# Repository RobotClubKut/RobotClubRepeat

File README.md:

# RobotClubRepeat
ろぼっとくらぶ りぴ～と

キャチロボがんばりましょう

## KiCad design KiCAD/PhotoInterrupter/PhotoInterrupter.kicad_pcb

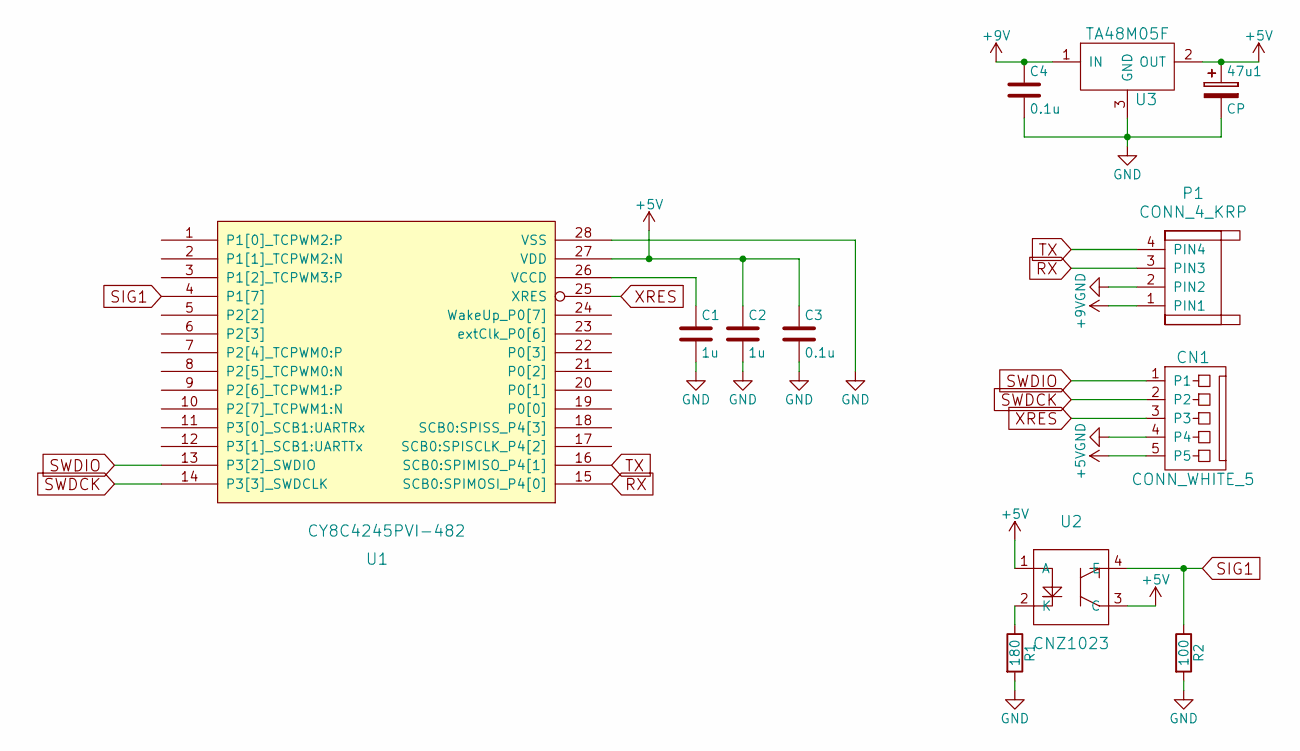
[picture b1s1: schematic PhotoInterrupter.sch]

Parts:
47u1: CP; C_Radial_D5_L6_P2.5
C1, C2: 1u; C_0805
C3, C4: 0.1u; C_0603
CN1: CONN_WHITE_5; DF1E-5P_Streight
P1: CONN_4_KRP; DF1E-4P_Streight
R1: 180; Diode_DO-41_SOD81_Vertical_AnodeUp
R2: 100; Diode_DO-41_SOD81_Vertical_AnodeUp
U1: CY8C4245PVI-482; SSOP-28_5.3x10.2mm_Pitch0.65mm
U2: CNZ1023
U3: TA48M05F; TO-251

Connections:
+5V: 47u1.1, C2.1, C3.1, CN1.5, U1.27 (VDD), U2.1 (A), U2.3 (C), U3.2 (OUT)
+9V: C4.1, P1.1 (PIN1), U3.1 (IN)
GND: 47u1.2, C1.2, C2.2, C3.2, C4.2, CN1.4, P1.2 (PIN2), R1.2, R2.2, U1.28 (VSS), U3.3 (GND)
unnamed: C1.1, U1.26 (VCCD)
unnamed: R1.1, U2.2 (K)
RX: P1.3 (PIN3), U1.15 (SCB0:SPIMOSI_P4[0])
SIG1: R2.1, U1.4 (P1[7]), U2.4 (E)
SWDCK: CN1.2, U1.14 (P3[3]_SWDCLK)
SWDIO: CN1.1, U1.13 (P3[2]_SWDIO)
TX: P1.4 (PIN4), U1.16 (SCB0:SPIMISO_P4[1])
XRES: CN1.3, U1.25 (XRES)

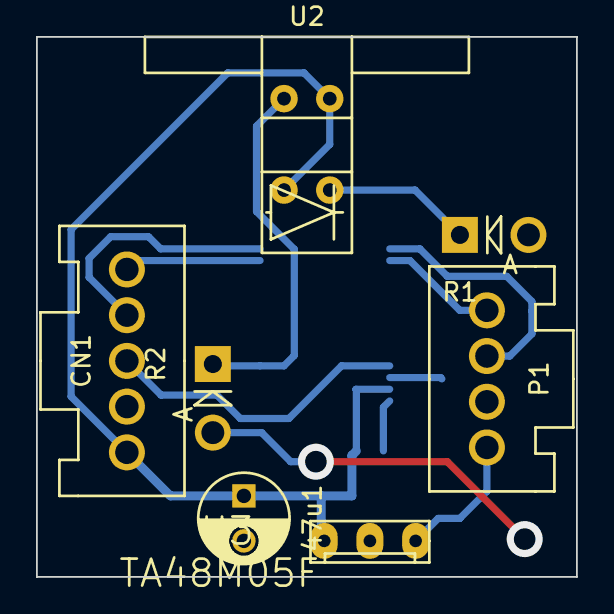
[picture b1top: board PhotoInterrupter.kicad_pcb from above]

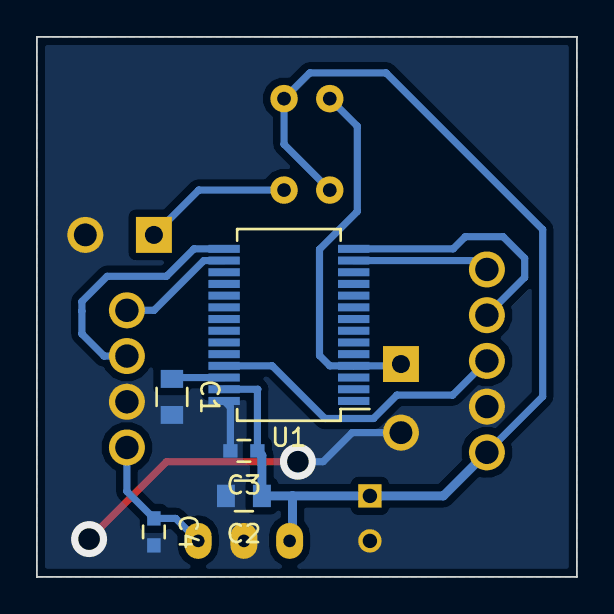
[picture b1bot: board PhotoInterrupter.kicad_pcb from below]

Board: 2 copper layers, 30.0 x 30.0 mm, 12 parts (5 on the bottom side), 11 nets.

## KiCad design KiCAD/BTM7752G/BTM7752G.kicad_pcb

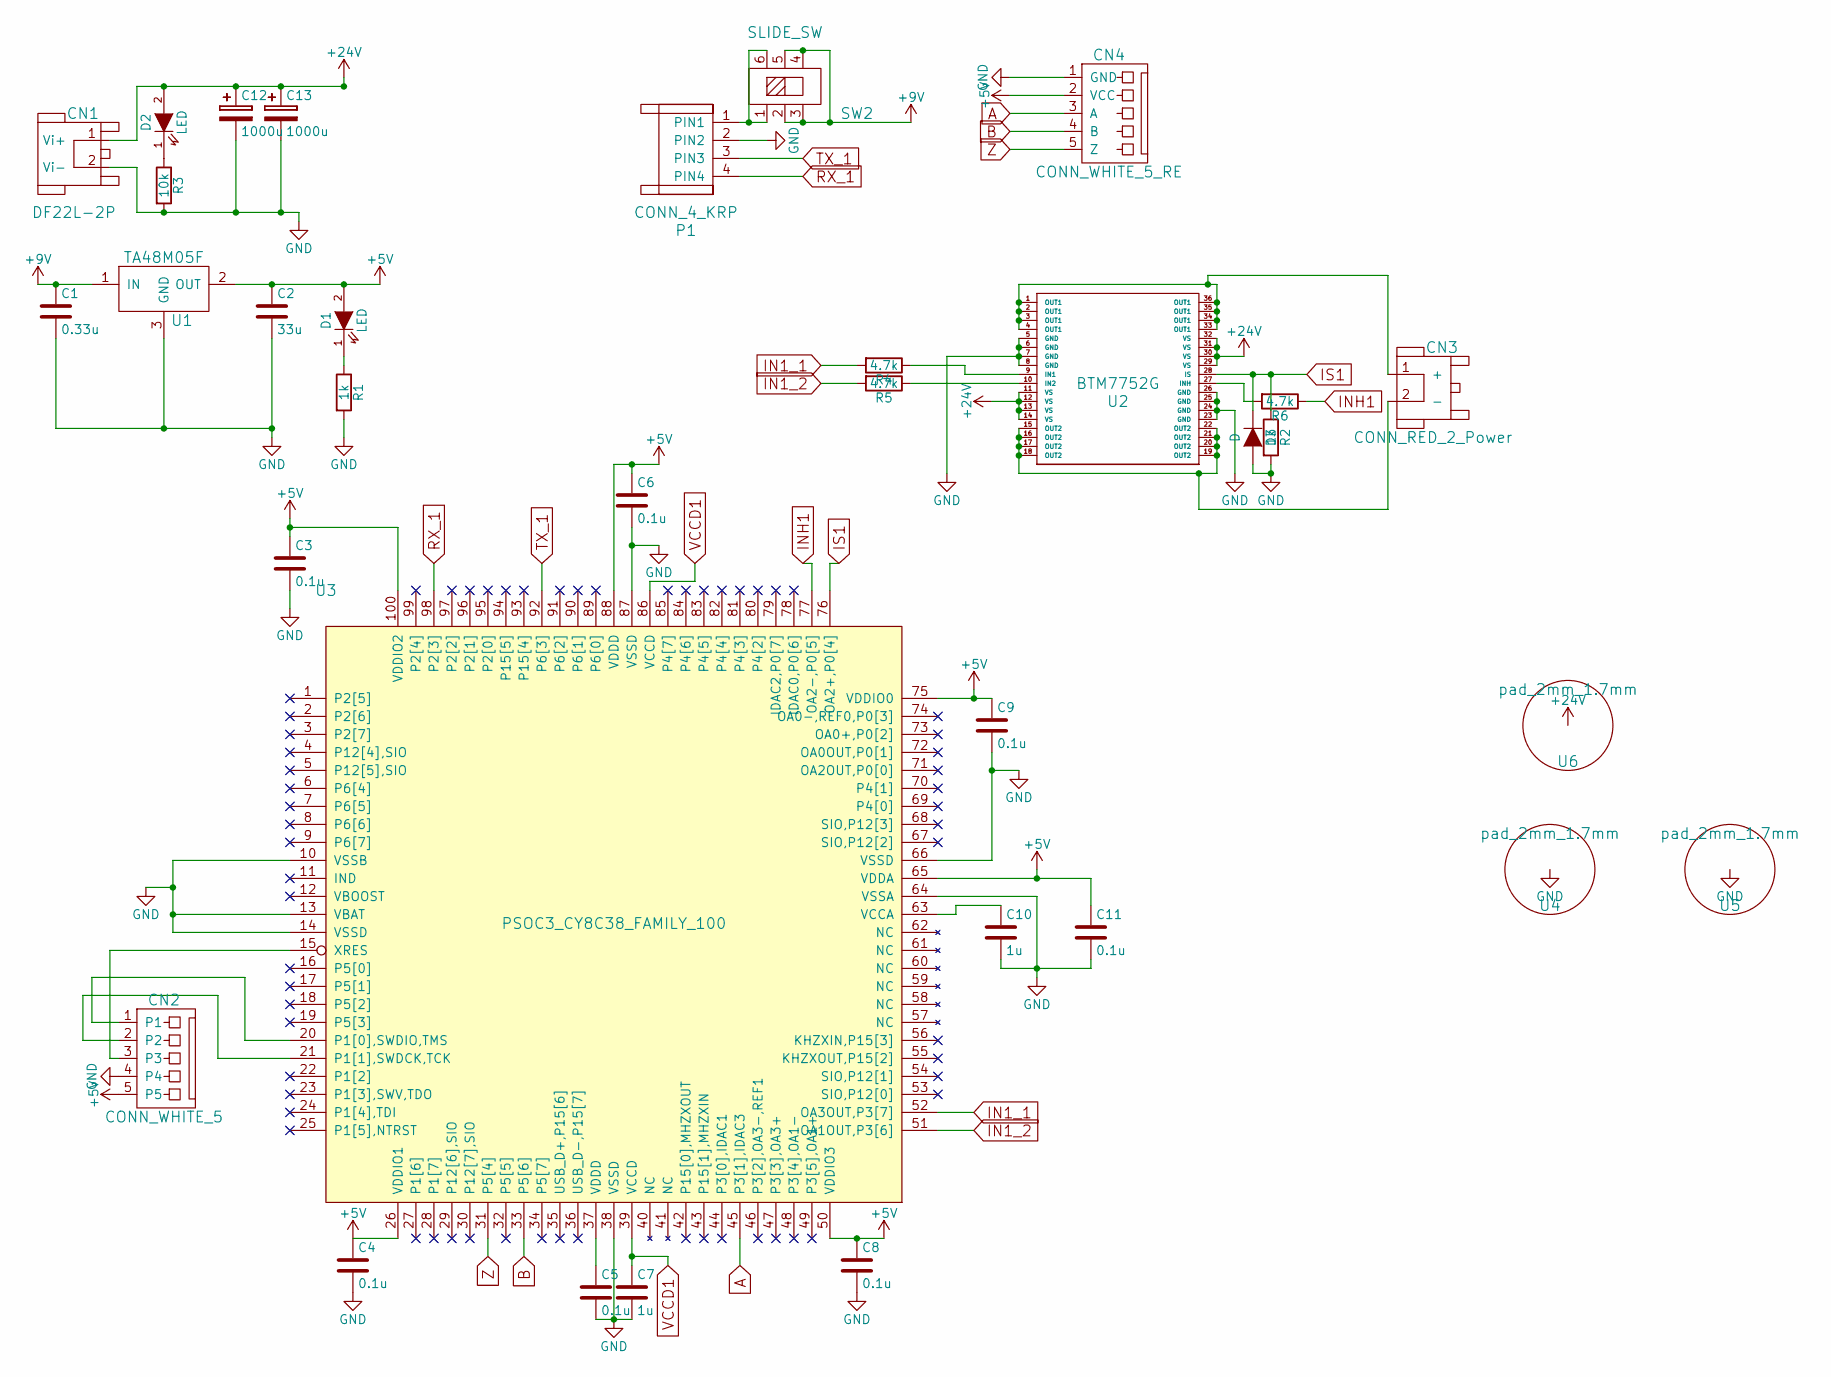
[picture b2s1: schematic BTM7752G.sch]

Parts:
C1: 0.33u; C_0603
C2: 33u; C_Radial_D5_L6_P2.5
C3, C4, C5, C6, C8, C9, C11: 0.1u; C_0603
C7, C10: 1u; C_0805
C12: 1000u; C_Radial_D18_L36_P7.5_Horizon5
C13: 1000u; C_Radial_D18_L36_P7.5_Horizon6
CN1: DF22L-2P; CONN_RED_2P_STRAIGHT
CN2: CONN_WHITE_5; DF1E-5P_Streight
CN3: CONN_RED_2_Power; CONN_RED_2P_STRAIGHT
CN4: CONN_WHITE_5_RE; DF1E-5P_Streight
D1, D2: LED; LED-3MM
D3: D; SOD-523_1
P1: CONN_4_KRP; DF1E-4P_Streight
R1, R2: 1k; R_0603
R3: 10k; R_0603
R4, R5, R6: 4.7k; R_0603
SW2: SLIDE_SW; Slide_Switch_SMD
U1: TA48M05F; HSOP3-P-2
U2: BTM7752G; PG-DSO-36
U3: PSOC3_CY8C38_FAMILY_100; TQFP-100_14x14mm_Pitch0.5mm
U4, U5, U6: pad_2mm_1.7mm

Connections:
+5V: C2.1, C3.1, C4.1, C6.1, C8.1, C9.1, C11.1, CN2.5, CN4.2 (VCC), D1.2 (A), U1.2 (OUT), U3.26 (VDDIO1), U3.50 (VDDIO3), U3.65 (VDDA), U3.75 (VDDIO0), U3.88 (VDDD), U3.100 (VDDIO2)
+9V: C1.1, SW2.2, SW2.3, SW2.4, SW2.5, U1.1 (IN)
+24V: C12.1, C13.1, CN1.1 (Vi+), D2.2 (A), U2.11 (VS), U2.12 (VS), U2.13 (VS), U2.14 (VS), U2.29 (VS), U2.30 (VS), U2.31 (VS), U2.32 (VS), U6.1
A: CN4.3 (A), U3.45 (P3[1],IDAC3)
B: CN4.4 (B), U3.33 (P5[6])
GND: C1.2, C2.2, C3.2, C4.2, C5.2, C6.2, C7.2, C8.2, C9.2, C10.2, C11.2, C12.2, C13.2, CN1.2 (Vi-), CN2.4, CN4.1 (GND), D3.2 (A), P1.2 (PIN2), R1.2, R2.2, R3.2, U1.3 (GND), U2.5 (GND), U2.6 (GND), U2.7 (GND), U2.8 (GND), U2.23 (GND), U2.24 (GND), U2.25 (GND), U2.26 (GND), U3.10 (VSSB), U3.13 (VBAT), U3.14 (VSSD), U3.38 (VSSD), U3.64 (VSSA), U3.66 (VSSD), U3.87 (VSSD), U4.1, U5.1
IN1_1: R4.2, U3.52 (OA3OUT,P3[7])
IN1_2: R5.2, U3.51 (OA1OUT,P3[6])
INH1: R6.1, U3.77 (OA2-,P0[5])
IS1: D3.1 (K), R2.1, U2.28 (IS), U3.76 (OA2+,P0[4])
unnamed: C5.1, U3.37 (VDDD)
unnamed: C10.1, U3.63 (VCCA)
unnamed: CN2.1, U3.20 (P1[0],SWDIO,TMS)
unnamed: CN2.2, U3.21 (P1[1],SWDCK,TCK)
unnamed: CN2.3, U3.15 (XRES)
unnamed: CN3.1 (+), U2.1 (OUT1), U2.2 (OUT1), U2.3 (OUT1), U2.4 (OUT1), U2.33 (OUT1), U2.34 (OUT1), U2.35 (OUT1), U2.36 (OUT1)
unnamed: CN3.2 (-), U2.15 (OUT2), U2.16 (OUT2), U2.17 (OUT2), U2.18 (OUT2), U2.19 (OUT2), U2.20 (OUT2), U2.21 (OUT2), U2.22 (OUT2)
unnamed: D1.1 (K), R1.1
unnamed: D2.1 (K), R3.1
unnamed: P1.1 (PIN1), SW2.1, SW2.6
unnamed: R4.1, U2.9 (IN1)
unnamed: R5.1, U2.10 (IN2)
unnamed: R6.2, U2.27 (INH)
RX_1: P1.4 (PIN4), U3.98 (P2[3])
TX_1: P1.3 (PIN3), U3.92 (P6[3])
VCCD1: C7.1, U3.39 (VCCD), U3.86 (VCCD)
Z: CN4.5 (Z), U3.31 (P5[4])

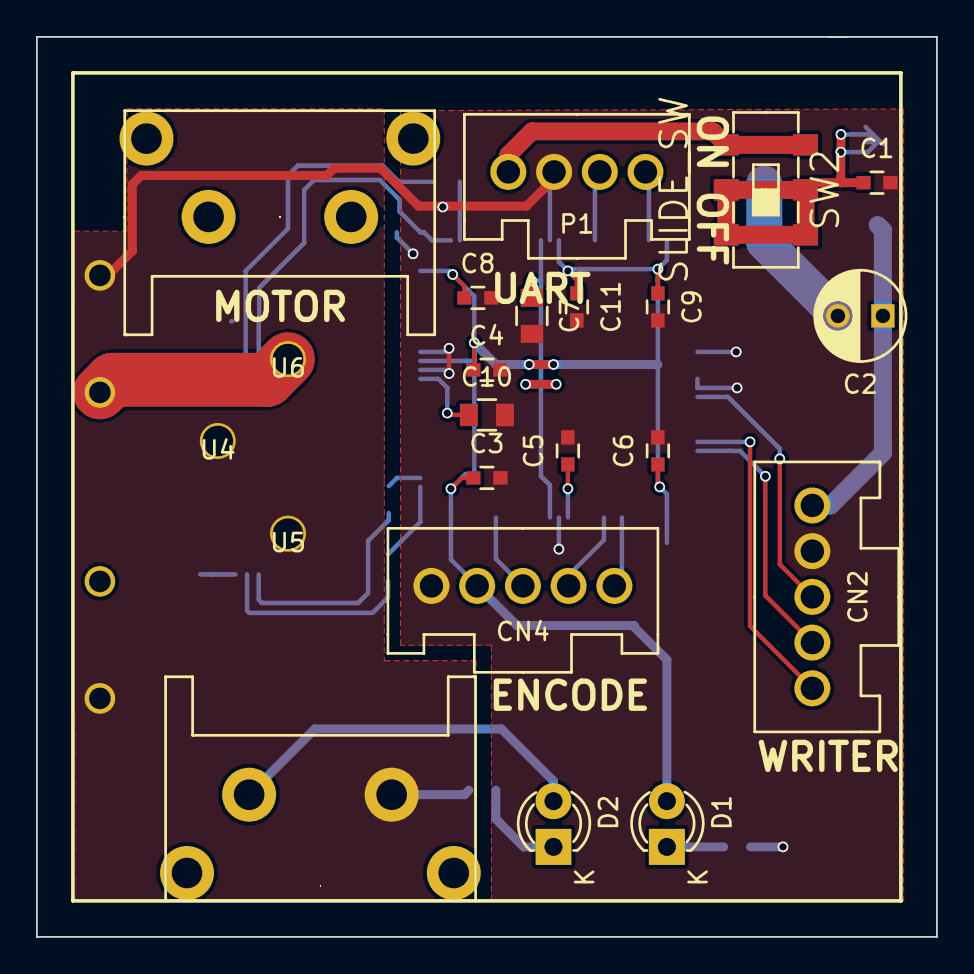
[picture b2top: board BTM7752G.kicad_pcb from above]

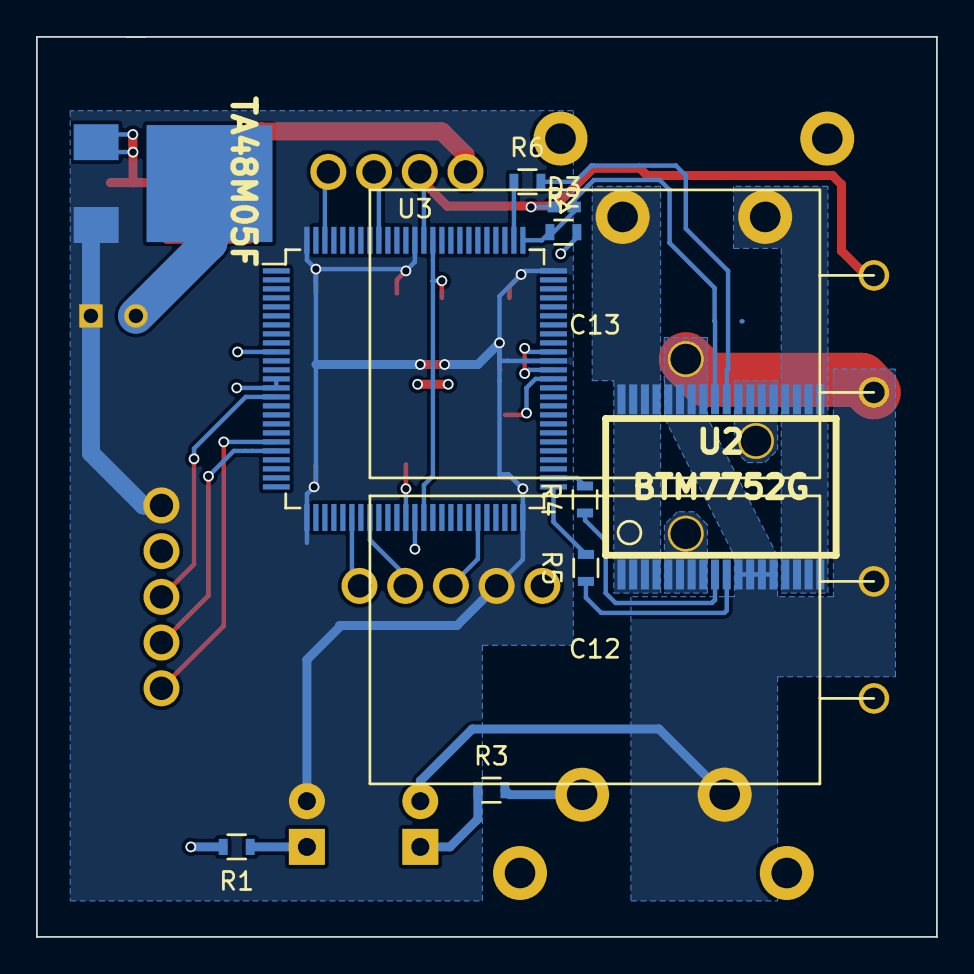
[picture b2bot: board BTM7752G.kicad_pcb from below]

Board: 2 copper layers, 50.0 x 50.0 mm, 34 parts (12 on the bottom side), 27 nets.

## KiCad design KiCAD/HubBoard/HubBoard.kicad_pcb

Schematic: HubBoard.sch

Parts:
C3, C4, C5, C7, C8, C10, C16, C17, C18, C22, C24, C25, C26, C28, C29: 0.1u; C_0603
C6, C11, C19, C23: 1u; C_0805
C9: 470p; C_Disc_D6_P5
C12, C13, C20, C21: 12p; C_0603
C27: 33u; C_Radial_D5_L6_P2.5
CN1, CN3: CONN_WHITE_5; DF1E-5P_Streight
CN2: DF22L-2P; CONN_RED_2P
CN4: DF22R-2P; CONN_RED_2P
CN5, CN6: CONN_WHITE_3; DF1E-3P_Streight
CP1: 470u; C_Radial_D10_L13_P5
CP2: 100u; C_Radial_D10_L13_P5
D1: D; Diode_DO-41_SOD81_Vertical_AnodeUp
D2: LED; LED-3MM
D3, D4, D7, D8, D9, D10: LED; LED-0603
L1: 220u; C_Radial_D10_L20_P5
R1: 1k; Resistor_Horizontal_RM10mm
R2: 6.2k; Resistor_Horizontal_RM10mm
R3: 0.33; Resistor_Horizontal_RM10mm
R4: R; R_0603
R5, R6, R9, R10, R11, R12: 1k; R_0603
SW1: SLIDE_SW; Toggle_Swith
U1, U2, U3, U4: DF3_UART; DF1E-4P_Streight
U5: TA48M05F; TO-251
U6: NJM2360A; PDIP-8
U7: Mini-B; USB_MINI_B_HIROSE
U8, U10: PSOC3_CY8C38_FAMILY_100; TQFP-100_14x14mm_Pitch0.5mm
U9, U11, U12, U13: drill_3mm; dril_3mm
Y1, Y2: Crystal; Crystal_HC49-SD_SMD

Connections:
+5V: C3.1, C4.1, C5.1, C7.1, C8.1, C16.1, C18.1, C22.1, C24.1, C25.1, C27.1, C28.1, C29.1, CN1.5, CN3.5, D2.2, U5.2 (OUT), U8.26 (VDDIO1), U8.50 (VDDIO3), U8.65 (VDDA), U8.75 (VDDIO0), U8.88 (VDDD), U8.100 (VDDIO2), U10.26 (VDDIO1), U10.50 (VDDIO3), U10.65 (VDDA), U10.75 (VDDIO0), U10.88 (VDDD), U10.100 (VDDIO2)
+9V: C26.1, CP1.1, L1.1, R2.1, U1.1 (VCC), U2.1 (VCC), U3.1 (VCC), U4.1 (VCC), U5.1 (IN)
+24V: CP2.1, R3.1, SW1.3, U6.6 (V+)
/bus0: U8.98 (P2[3]), U10.89 (P6[0])
/bus1: U8.97 (P2[2]), U10.90 (P6[1])
/bus2: U8.96 (P2[1]), U10.91 (P6[2])
/bus3: U8.95 (P2[0]), U10.92 (P6[3])
/bus4: U8.94 (P15[5]), U10.93 (P15[4])
/bus5: U8.93 (P15[4]), U10.94 (P15[5])
/bus6: U8.92 (P6[3]), U10.95 (P2[0])
/bus7: U8.91 (P6[2]), U10.96 (P2[1])
/bus8: U8.90 (P6[1]), U10.97 (P2[2])
/bus9: U8.89 (P6[0]), U10.98 (P2[3])
GND: C3.2, C4.2, C5.2, C6.2, C7.2, C8.2, C9.2, C10.2, C11.2, C12.2, C13.2, C16.2, C17.2, C18.2, C19.2, C20.2, C21.2, C22.2, C23.2, C24.2, C25.2, C26.2, C27.2, C28.2, C29.2, CN1.4, CN2.2, CN3.4, CN4.1, CN5.1, CN6.1, CP1.2, CP2.2, D1.2 (A), R1.1, R4.2, R5.1, R6.1, R9.2, R10.1, R11.2, R12.1, U1.2 (GND), U2.2 (GND), U3.2 (GND), U4.2 (GND), U5.3 (GND), U6.4 (GND), U7.5 (GND), U8.10 (VSSB), U8.13 (VBAT), U8.14 (VSSD), U8.38 (VSSD), U8.64 (VSSA), U8.66 (VSSD), U8.87 (VSSD), U10.10 (VSSB), U10.13 (VBAT), U10.14 (VSSD), U10.38 (VSSD), U10.64 (VSSA), U10.66 (VSSD), U10.87 (VSSD)
unnamed: C6.1, U8.63 (VCCA)
unnamed: C9.1, U6.3 (Ct)
unnamed: C10.1, U8.37 (VDDD)
unnamed: C12.1, U8.42 (P15[0],MHZXOUT), Y1.2
unnamed: C13.1, U8.43 (P15[1],MHZXIN), Y1.1
unnamed: C17.1, U10.37 (VDDD)
unnamed: C20.1, U10.42 (P15[0],MHZXOUT), Y2.2
unnamed: C21.1, U10.43 (P15[1],MHZXIN), Y2.1
unnamed: C23.1, U10.63 (VCCA)
unnamed: CN1.1, U8.20 (P1[0],SWDIO,TMS)
unnamed: CN1.2, U8.21 (P1[1],SWDCK,TCK)
unnamed: CN1.3, U8.15 (XRES)
unnamed: CN2.1, CN4.2, SW1.1, SW1.2
unnamed: CN3.1, U10.20 (P1[0],SWDIO,TMS)
unnamed: CN3.2, U10.21 (P1[1],SWDCK,TCK)
unnamed: CN3.3, U10.15 (XRES)
unnamed: CN5.2, U8.25 (P1[5],NTRST)
unnamed: CN5.3, U8.24 (P1[4],TDI)
unnamed: CN6.2, U8.52 (OA3OUT,P3[7])
unnamed: CN6.3, U8.51 (OA1OUT,P3[6])
unnamed: D1.1 (K), L1.2, U6.2 (Es)
unnamed: D2.1, R4.1
unnamed: D3.1, R5.2
unnamed: D3.2, U8.77 (OA2-,P0[5])
unnamed: D4.1, R6.2
unnamed: D4.2, U8.76 (OA2+,P0[4])
unnamed: D7.1, R9.1
unnamed: D7.2, U10.5 (P12[5],SIO)
unnamed: D8.1, R10.2
unnamed: D8.2, U10.6 (P6[4])
unnamed: D9.1, R11.1
unnamed: D9.2, U10.7 (P6[5])
unnamed: D10.1, R12.2
unnamed: D10.2, U10.8 (P6[6])
unnamed: R3.2, U6.1 (Cs), U6.7 (Si), U6.8 (Cd)
unnamed: U7.2 (D-), U8.36 (USB_D-,P15[7])
unnamed: U7.3 (D+), U8.35 (USB_D+,P15[6])
RX_1: U1.4 (RX), U10.29 (P12[6],SIO)
RX_2: U2.4 (RX), U10.27 (P1[6])
RX_3: U3.4 (RX), U10.33 (P5[6])
RX_4: U4.4 (RX), U10.31 (P5[4])
TX_1: U1.3 (TX), U10.30 (P12[7],SIO)
TX_2: U2.3 (TX), U10.28 (P1[7])
TX_3: U3.3 (TX), U10.34 (P5[7])
TX_4: U4.3 (TX), U10.32 (P5[5])
VCCD1: C11.1, U8.39 (VCCD), U8.86 (VCCD)
VCCD2: C19.1, U10.39 (VCCD), U10.86 (VCCD)
Vth: R1.2, R2.2, U6.5 (INV)

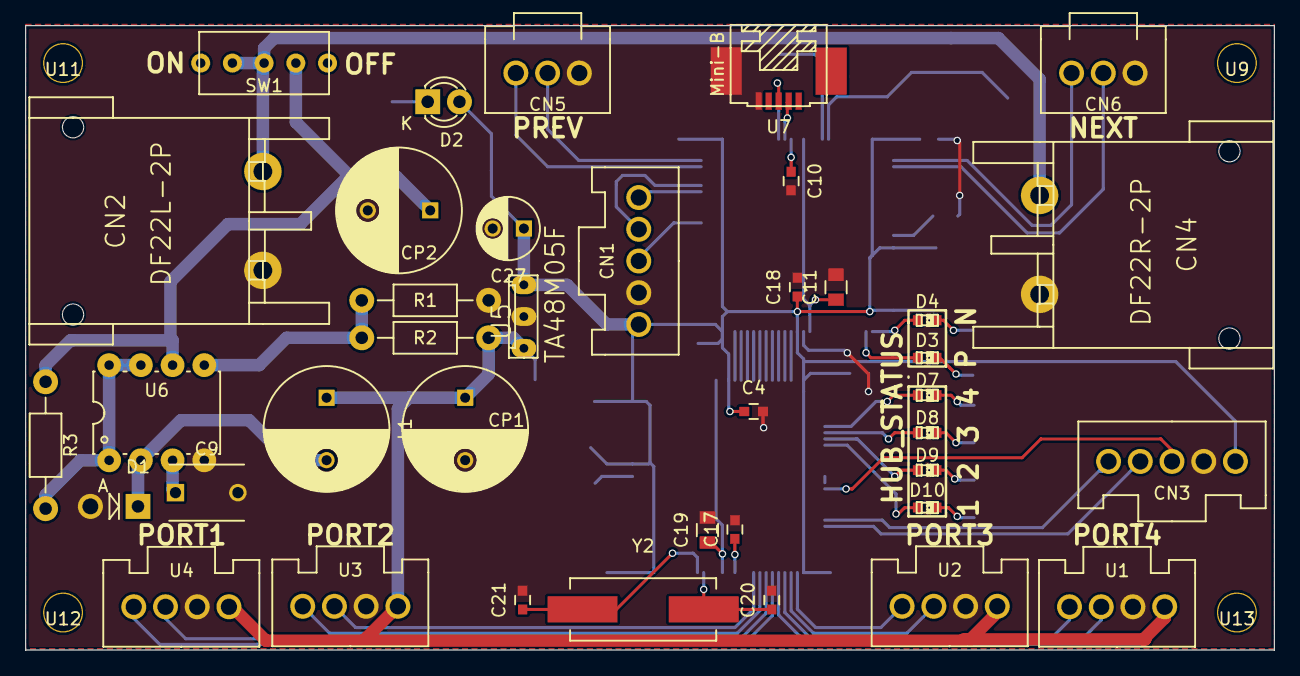
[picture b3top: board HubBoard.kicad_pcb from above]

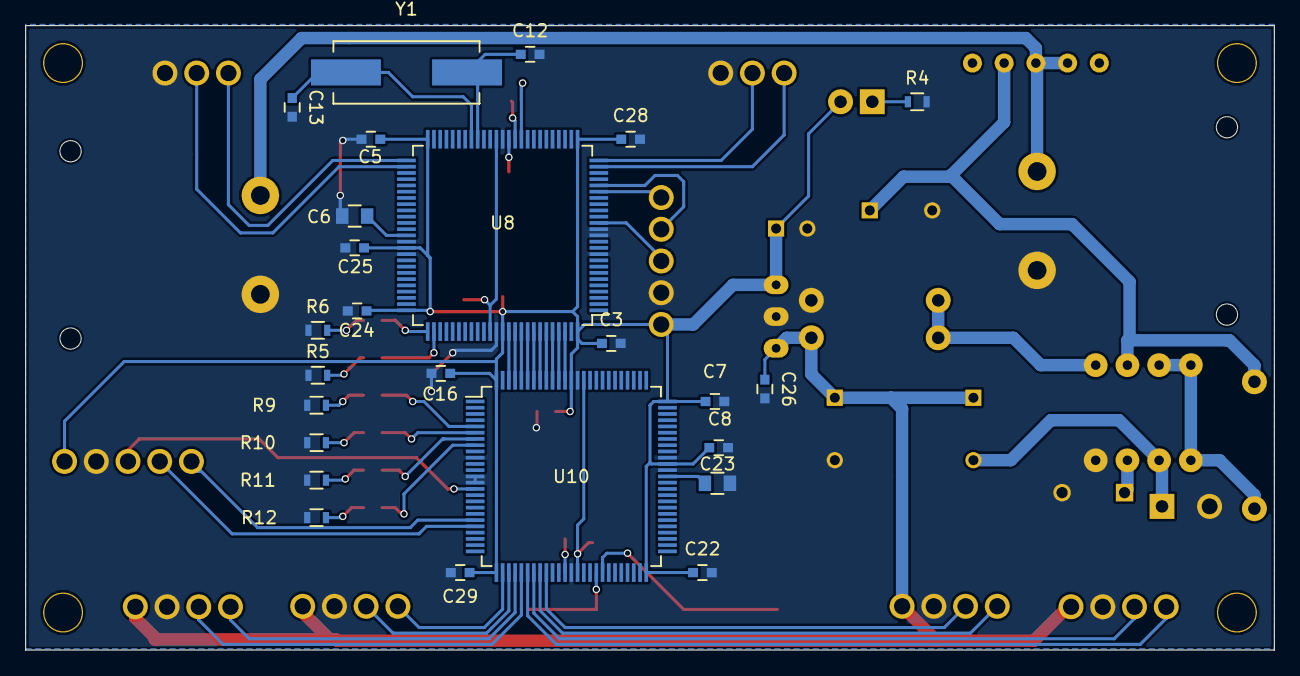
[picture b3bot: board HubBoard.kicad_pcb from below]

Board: 2 copper layers, 100.0 x 50.0 mm, 68 parts (25 on the bottom side), 62 nets.

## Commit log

2015-06-05 UART TX DMA TEST
2015-06-11 回路図未完
2015-06-11 回路図みかん
2015-06-21 add uart-hub project
2015-06-21 b_dma_uart bug fix
2015-06-22 update uart-hub test
2015-06-22 crc bug fix
2015-06-22 add crc_uart
2015-06-23 crc_uart bug fix
2015-07-03 add spi-test
2015-07-04 update spi-test
2015-07-05 add custum spim
2015-07-09 add spi hfc
    Hardware Flow Control SPI
    *Timing bug exist
2015-07-12 update spim
2015-07-23 new branch
2015-07-23 new branch board6x9
2015-07-25 5x10半分完成
2015-07-26 board modify
2015-07-27 silk add
2015-07-30 add board BTM7752G
2015-08-01 モータドライバ完成（仮）
2015-08-07 add UART-HUB_Slave project
2015-08-09 add memo
2015-08-09 とりあえず書いた
2015-08-09 データを返すだけの slave program
2015-08-09 動いてるように見えるバッファ関連がおかしいかも
2015-08-10 add version.txt
2015-08-18 add UART_S
2015-08-18 add UART_HUB_SPI_TEST
2015-08-24 SPI DMAでけた
2015-08-24 SPIM TX DMA でけた
2015-08-25 SPIS TX と SPIM RXのDMAでけた
2015-08-30 create CatchRobo_master
2015-08-30 update kicad
2015-08-30 master to slave通信出来たよ
2015-08-30 slave state add
2015-08-30 new add slave and master
2015-09-01 手動割り当て出来た
2015-09-01 手動動作確認済
    リミットスイッチがたまに反応しない
2015-09-01 リミットスイッチ直した
    リミットスイッチのピンを変更して解決
2015-09-03 読みやすくした
    動作確認済
2015-09-04 manual BaseMotion 関数化したよ
2015-09-04 armslave 初期位置移動 追加
2015-09-04 Manual Control完成
2015-09-05 半自動のテンプレートできた
2015-09-05 半自動化完成
2015-09-05 add comment
2015-09-06 ステートの動作変更
2015-09-07 安定して動く
